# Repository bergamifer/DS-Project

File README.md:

# DS-Project — Beamforming Audio (firmware + hardware)

Sistema de audio beamforming de 32 canales basado en **STM32H743** + **ESP32-C3-MINI-1**.
Control via WiFi (HTTP), pipeline DMA circular, latencia ~20 ms extremo a extremo.

Es el hardware de **Domosónica**, una instalación sonora de ~500 parlantes: cada placa es
un nodo autónomo de 32 canales, y la obra son ~18 nodos en red.

> **Repo unificado (2026-07-03):** este repo (antes `DS-Firmware`, ahora **privado**
> como `DS-Project`) incorpora el proyecto KiCad de hardware completo en
> [`hardware/DS/`](hardware/DS/) — historial de commits preservado vía `git subtree`
> desde el repo `DS` original. Un solo lugar para firmware (STM32 + ESP32) y diseño
> de PCB.

> **¿Primera vez con el equipo?** Empezá por la [guía de uso y conexionado](docs/guia_operacion.md) —
> está escrita en lenguaje llano, sin dar por sabido nada de audio ni de electrónica.
> Y antes de encender amplificadores con micrófonos enchufados, leé
> [qué modos hacen acople](tools/README.md).

---

## Dónde está el proyecto hoy (2026-09-11)

| | Estado |
|---|---|
| **DS11** | **En operación, 3 placas.** 32 canales poblados, audio limpio, soak de 19,6 h |
| **DS12** | **En diseño.** Es la tirada de 10 unidades. Etapa de fuente rediseñada, auditoría cerrada |
| Beamforming | Implementado y **medido**: contraste +17,7 dB dentro/fuera del foco |
| Banco de medición | Dos micrófonos fijos sobre trama TDM común — el foco se verifica con números, no a oído |
| App iOS / sitio público | Andando ([`ios/`](ios/), [`sitio/`](sitio/)) |

El registro de por qué se decidió cada cosa está en los reportes mensuales:
[julio](docs/reporte_2026-07.md) · [agosto](docs/reporte_2026-08.md) · [septiembre](docs/reporte_2026-09.md).

---

## Hardware

| Componente | Detalle |
|---|---|
| MCU | STM32H743VIT6 (LQFP100), Cortex-M7 @ 480 MHz, VOS0 |
| WiFi Bridge | ESP32-C3-MINI-1 (UART4 @ 115200, PA0/PA1) |
| DACs | 4× PCM1690 (8ch TDM8 c/u) = 32 canales — I2C1: 0x98, 0x9C, 0x9A, 0x9E |
| ADC | AK5538VN (8ch TDM256) via SAI3_B — I2C3 addr 0x22 (7-bit 0x11) |
| Amps | 32× PAM8302A Class-D 2.5W (shutdown compartido PD3) |
| EEPROM | CAT24C256 (I2C4 PB6/PB7 **AF6**, WP=PB5) |
| Power | 20V → buck → 5VA → 3.3V/3.3VA (DS12: dos bucks en paralelo; fuente de 24 V, nunca más de 25,5 V: `hardware/DS/DS12_ENTRADA_24V.md`) |

> En DS12 la etapa de fuente cambia entera: el buck pasa a **AP63356** y el LDO digital
> desaparece. El diseño completo, con valores y por qué, está en
> [`hardware/DS/DS12_ALIMENTACION.md`](hardware/DS/DS12_ALIMENTACION.md).

---

## Arquitectura de Audio

```
AK5538VN (ADC 8ch)
    |  TDM256 32-bit @ 48 kHz (config TDM por I2C3, addr 0x22)
    v
SAI3_B RX (Master) --- DMA1_Stream4 --> audio_buffer_3b_rx (RAM_D2)
    |
    v
delay_line[8][1024]   <- circular, 8 canales
    |  Process_ADC_Half() deinterleave + (>>8 a 24-bit)
    v
Fill_Audio_Beamform()   <- per-channel: delay / gain[0-255] / mute
    |                       (test tone -30dBFS cuando test_tone_enabled=1)
    |---> SAI1_A + SAI1_B  (ch 0-15)   DMA1_Stream0 / Stream3
    '---> SAI2_A + SAI2_B  (ch 16-31)  DMA1_Stream1 / Stream2
              |
              v
        4× PCM1690 DAC --> 32× PAM8302A --> parlantes
```

**Latencia total:** ~20,1 ms (10 ms DMA input + ~0,13 ms compute + 10 ms DMA output)

> **⚠️ Alineamiento SAI:** con `DataSize=24` el SAI transmite bits [23:0] (right-aligned).
> Los samples se escriben directo, **sin `<<8`**. El `<<8` erróneo (heredado de DS9) causaba
> la distorsión "tipo 50 kHz" — ver bring-up findings §1.

---

## SAI — pinout DS10/DS11 (idéntico; DS10 corrigió los errores de DS9)

| Bloque | Modo | Pines (AF) | Canales | DMA |
|---|---|---|---|---|
| SAI1_A | Master TX TDM8 | PE4(FS) PE5(SCK) PE6(SD) — AF6 | 0-7 | DMA1_S0 req87 |
| SAI1_B | Slave TX sync | PE3(SD) — AF6 | 8-15 | DMA1_S3 req88 |
| SAI2_A | Master TX TDM8 | PD12(FS) PD13(SCK) PD11(SD) — AF10 | 16-23 | DMA1_S1 req89 |
| SAI2_B | Slave TX sync | PE11(SD) — AF10 | 24-31 | DMA1_S2 req90 |
| SAI3_B | Master RX TDM256 | PD8(SCK) PD9(SD) PD10(FS) — AF6 | ADC 8ch | DMA1_S4 req114 |
| PE2 | MCLK out (24.576 MHz) | SAI1_MCLK_A — AF6 | — | — |

Mapa completo de pines: [docs/pin_map.md](docs/pin_map.md).

---

## ESP32-C3 — Protocolo UART

Trama binaria @ 115200 8N1 (GPIO0 TX → PA1 RX, GPIO1 RX ← PA0 TX):

```
[0xAA][0x55][CMD][LEN_L][LEN_H][PAYLOAD...][XOR_CHECKSUM][0x0D][0x0A]

CMD 0x01 = UPDATE_CFG (52 bytes payload)
  Byte  0    : master_gain (0-255)
  Byte  1    : mute_global (0/1)
  Bytes 2-33 : delays[16] x uint16 LE
  Bytes 34-49: gains[16]  x uint8      (0-255, 0xFF = unity)
  Bytes 50-51: mutes      x uint16 LE  (bitfield ch0-15)
```

HTTP endpoints: `POST /command` (config JSON), `GET /status`, `GET /ping`

> **Trampa de la API:** `POST /reset` **no reinicia el chip** — es un reset de fábrica, y
> deja la placa en modo 0, que es el del acople. Para reiniciar de verdad: `make ota`.

---

## Build & Flash

```bash
# STM32 (firmware principal) — TARGET = ds11_beamforming
cd firmware && make -j4
make flash-stlink            # st-flash --reset (arranca solo)
make todo-cube               # bootloader + app con CubeProgrammer
make ota OTA_HOST=192.168.100.77   # por WiFi, sin cables

# Debug serial: UART7 (PE7/PE8) → J7 → VCP del ST-Link
screen /dev/cu.usbmodemXXXX 115200

# ESP32-C3
. $HOME/esp/esp-idf/export.sh
cd firmware_esp32c3 && idf.py flash monitor -p /dev/cu.usbmodemYYYY
# o, desde firmware/:  make esp-flash
```

⚠️ **`st-flash` no sirve en todas las placas** — en la segunda y la tercera hay que usar
CubeProgrammer (`make todo-cube`). Ver las notas de cada placa en la memoria del proyecto.

**La app vive en `0x08020000`, no en `0x08000000`**: hay un bootloader propio adelante
(ver [docs/ota_wifi.md](docs/ota_wifi.md)).

---

## Estructura del Repositorio

```
hardware/DS/                    # Proyecto KiCad completo (historial propio via subtree)
  DS.kicad_pro/.kicad_sch/.kicad_pcb   # Esquematico + PCB activo
  DS.kicad_dru                  # Reglas de diseño propias (el QFN de IC3) — ver el README de ahi
  DS12_CHECKLIST.md             # LA LISTA PARA TILDAR mientras se dibuja — el indice de los otros tres
  DS12_ALIMENTACION.md          # LA ETAPA DE FUENTE de la DS12: que comprar y como dibujarla
  DS12_PLANNING.md              # Backlog de la DS12 (geometria 2x16, arnes, correcciones)
  DS12_AUDITORIA.md             # Auditoria previa a fabricar: 12 dimensiones, solo lo verificado
  DS12_USB_STM32.md             # USB del STM32 (PA11/PA12 hoy al aire)
  DS11_RELEASE.md               # El KiCad de lo que se fabrico, verificado contra los gerbers
  DS11_PLANNING.md, DS10_*.md   # Historico de revisiones
  jlcpcb/production_files/      # BOM y CPL REALES — la verdad sobre part numbers, no el netlist
  DS.txt                        # Netlist exportado (entrada de tools/netlist_digest.py)
  datasheets/, librerias/, 3d/, plot/, Versiones/

firmware/                       # STM32H743 — make -j4, TARGET=ds11_beamforming
  Core/Src/main.c               # Pipeline SAI/DMA + beamforming + AUTOFOCUS + geometria del array
  Core/Src/uart_protocol.c      # Protocolo binario ESP32<->STM32
  Core/Src/pcm1690.c            # Driver I2C de los 4 DAC
  Core/Src/eeprom_config.c      # Persistencia de config (I2C4 AF6)
  Core/Inc/pin_definitions.h    # Fuente de verdad de todos los pines

firmware_esp32c3/               # ESP32-C3: WiFi + HTTP + puente UART + UI web embebida

tools/                          # Herramientas de host (medicion + hardware) — ver tools/README.md
  check_pcb.sh                  # HOOK: impide commitear gerbers con el cobre desactualizado
  netlist_digest.py             # Convierte DS.txt en tres archivos grepables
  geometria_array.py            # Las 32 posiciones de parlante + DXF del panel, leidas de main.c
  nivel.py abx.py fase.py ...   # Medicion acustica por HTTP (ninguna enciende amps sola)

docs/
  guia_operacion.md             # GUIA DE USO en lenguaje llano
  manual_modos.md               # Los modos de operacion, uno por uno
  reporte_2026-0{7,8,9}.md      # El camino recorrido y por que se decidio cada cosa
  banco_dos_microfonos.md       # El banco de medicion de dos microfonos
  protocolo_medicion.md         # Metodologia acustica (mic fijo, foco movil)
  ds11_errata.md                # Los cortos de fabrica de la DS11 — leer antes de mandar a producir
  ds11_perf.md                  # Performance del pipeline (caches, -O2, soak)
  pin_map.md, memory_map.md     # Pines y layout de RAM (regla DMA vs DTCM)
  ak5538vn_ref.md, pcm1690_ref.md, gpio_control.md, audio_architecture.md
  ota_wifi.md, multinode.md, app_ios.md, instalacion_15_nodos.md
  stm32/                        # Referencia RM0433 (clocks, SAI, DMA, I2C, GPIO)
  datos/                        # Mediciones crudas en JSON + el .md que dice que se medía
  img_osc/, media/              # Capturas de osciloscopio y video
  historico/                    # Bring-up DS10 + esquematico DS9
  pdf/                          # Plantilla y script para generar la guia en PDF

datasheets/                     # Hojas de datos del MCU y los chips de audio
webserver/                      # Control web multi-dispositivo (Flask + SQLite)
sitio/                          # Pagina publica del proyecto
ios/                            # App "Domosonica" (SwiftUI)
mecenazgo/                      # ~320 MB de comprobantes — FUERA de git a proposito
```

**Fuera del repo a propósito:** `firmware/build*/`, `firmware_esp32c3/build/`,
`webserver/venv/`, `mecenazgo/`, `.ds12_audit/` (derivado del netlist), `*.wav`,
`docs/pdf/*.pdf` (se regenera con `docs/pdf/hacer_pdf.sh`), y `secrets.h`.

---

## Antes de mandar una placa a producir

```bash
tools/check_pcb.sh --install    # una sola vez por copia del repo
```

Instala un hook de pre-commit que corre el DRC dos veces —con los rellenos guardados y
con `--refill-zones`— y **bloquea el commit si el cobre guardado está viejo**. KiCad no
recalcula los rellenos al plotear: usa lo que está guardado. Ese mecanismo ya arruinó dos
tandas de la DS11 ([docs/ds11_errata.md](docs/ds11_errata.md)) y apareció una tercera vez,
latente, en septiembre.

Al exportar los gerbers, además: `kicad-cli pcb export gerbers --check-zones` (viene
apagado por default).

---

## Issues Conocidos

| Problema | Estado |
|---|---|
| Skew de fase entre SAI1 y SAI2 (ch0-15 vs 16-31) | Medido: **4 µs** entre bancos. Sync por SAI_GCR si algún día molesta |
| Protocolo ESP32: config de 16ch / mutes 16-bit | `CMD_SET_BEAM`/`CMD_SET_MODE` cubren el uso normal; raw de 32ch pendiente |
| Underruns residuales (~4) en el bloque verboso de cada 10 s | Benignos (el DMA reusa el half-buffer) |
| PA11/PA12 (USB_DM/DP del STM32) al aire | Ver [DS12_USB_STM32.md](hardware/DS/DS12_USB_STM32.md) |
| Prueba de escucha del `-O2` | Pendiente desde la mejora de 43× del pipeline |

---

## Próximos Pasos

1. **Cerrar la DS12 y mandar a producir las 10 placas** — etapa de fuente + los ítems de
   esquemático del §3 de [DS12_AUDITORIA.md](hardware/DS/DS12_AUDITORIA.md)
2. Cortar y armar los nodos con la geometría **2×16** (el firmware ya la soporta:
   `SPK_LAYOUT_2X16` en `main.c`)
3. Control de volumen/balance per-canal vía ESP32 (registros 72-79 del PCM1690, hoy fijos
   en −24 dB por `PCM1690_ATTEN_DEFAULT`)
4. Instalación multi-nodo: [docs/multinode.md](docs/multinode.md) y
   [docs/instalacion_15_nodos.md](docs/instalacion_15_nodos.md)

---

**Última actualización:** 2026-09-11 — auditoría DS12 aplicada, orden del repo, hook de PCB.

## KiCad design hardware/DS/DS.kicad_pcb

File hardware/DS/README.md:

# Domosónica — la placa DS

Sistema de audio espacial de 32 canales con capacidad de beamforming, diseñado para instalaciones artísticas a gran escala.

---

## El proyecto

**Domosonica** es una instalación sonora inmersiva basada en un campo de ~500 parlantes distribuidos en el espacio. El objetivo es crear experiencias de escucha donde el sonido se percibe como un fenómeno espacial: fuentes que se mueven, campos que emergen, focos que aparecen y desaparecen en el espacio físico.

El beamforming permite dirigir energía sonora hacia puntos específicos del espacio sumando señales con retardos calculados. Con suficientes parlantes y resolución de fase, es posible construir frentes de onda arbitrarios — lo que convierte el espacio en un instrumento.

### Por qué hardware propio

La escala del proyecto (~500 parlantes) hace inviable el uso de hardware de audio profesional estándar: demasiado costoso, demasiado grande, demasiado dependiente de infraestructura. La placa DS es una solución diseñada específicamente para esta instalación: barato, compacto, reproducible, y capaz de operar en red distribuida.

---

## La placa, por unidad

Cada unidad es un nodo de audio autónomo que distribuye 32 canales amplificados hacia 32 parlantes. La instalación completa usa ~18 unidades conectadas en red.

```
                         DS (por unidad)
┌────────────────────────────────────────────────────────┐
│                                                        │
│  20V DC ──> Buck ──> 5V ──> 32x PAM8302A ──> Speakers │
│              │                                         │
│              └──> LDOs ──> STM32H743 ──SAI──> 4x DAC  │
│                                │                       │
│                            ESP32-C3  (WiFi/BLE)        │
│                                │                       │
│                            AK5538VN  (8ch ADC)         │
│                                                        │
└────────────────────────────────────────────────────────┘
         ↑                              ↑
    20V daisy-chain              Cat5e/RJ45 audio
    entre cajas                  (4 links × 8ch = 32ch)
```

### Capacidades por unidad

- **32 canales de salida** — DAC diferencial 32-bit + amp Class-D 2.5W por canal
- **8 canales de entrada** — ADC diferencial 32-bit (micrófonos o señal de referencia)
- **Sincronización de red** — MCLK 24.576MHz (512xfS) compartido garantiza coherencia de fase entre unidades
- **WiFi/BLE** — configuración y control inalámbrico
- **Alimentación 20V** — bus daisy-chain entre cajas, un solo cable de potencia

### Escala del sistema completo

| | Por unidad | Sistema (18 unidades) |
| --- | --- | --- |
| Canales de salida | 32 | ~576 |
| Canales de entrada | 8 | ~144 |
| Parlantes | 32 | ~500 |
| Alimentación | 20V DC | Bus daisy-chain |

---

## Beamforming

El beamforming en este contexto no es telecomunicaciones — es síntesis de campo sonoro. La idea central es que si conocés la posición de cada parlante y podés controlar la fase y amplitud de cada canal de forma independiente, podés construir patrones de interferencia específicos en el espacio.

**Aplicaciones concretas en la instalación:**

- Focos de sonido: energía concentrada en un punto del espacio
- Fuentes virtuales: la percepción de que el sonido viene de un lugar donde no hay parlante
- Zonas silenciosas: cancelación activa por interferencia destructiva
- Movimiento: barrido de un frente de onda a través del espacio

El STM32H743 corre a 480MHz con DMA audio pipeline y opera los 5 puertos SAI simultáneamente sin underruns, lo que permite actualizar los 32 canales en tiempo real a 48kHz.

---

## Hardware

### Componentes principales

| IC | Función | Bus |
| --- | --- | --- |
| STM32H743VIT6 | MCU central, 480MHz, LQFP100 | — |
| 4× PCM1690 | DAC 8ch diferencial 32-bit | SAI1/SAI2 |
| AK5538VN | ADC 8ch diferencial 32-bit | SAI3_B (TDM256) |
| 32× PAM8302A | Amplificador Class-D 2.5W/ch | — |
| ESP32-C3-Mini | WiFi / BLE | UART |
| MP2315S | Buck 20V→5V 3A | — |

> **En DS12 la etapa de fuente cambia entera:** el buck pasa a **AP63356** y el LDO digital
> desaparece. Todo el diseño, con valores y con el porqué de cada uno, en
> [DS12_ALIMENTACION.md](DS12_ALIMENTACION.md).
>
> **Entrada de la DS12: 24 V, ajustada a 24,0 V y nunca más de 25,5 V** (decidido el 2026-10-23;
> detalle en [DS12_ENTRADA_24V.md](DS12_ENTRADA_24V.md)). Por debajo de ~15 V los amplificadores
> no encienden (el micro sí); por encima de ~26,7 V conduce el TVS y puede abrirse el fusible.
> **Esa regla es sólo de la DS12.** La DS11 nunca va a 24 V: su buck MP2315S aguanta 26 V como
> máximo absoluto. Antes este párrafo decía «20 V, ventana 15–21 V, 24 V no sirve»: ya no vale.

### PCB

- 4 capas, FR-4, 1.6mm — stackup JLC04161H-7628
- Fabricado por JLCPCB
- Diseñado en **KiCad 10.0** (el archivo dice `generator_version "10.0"`)

### Distribución de audio

Señal diferencial sobre Cat5e/RJ45 en topología daisy-chain. 4 pares trenzados por cable = 4 canales diferenciales. 2 cables por placa = 8 canales por enlace × 4 enlaces = 32 canales.

---

## Estado (2026-09-11)

| Versión | Estado |
| --- | --- |
| DS9 | Histórico — sistema base, PCM1802 2ch ADC |
| DS10 | Histórico. Tanda de 3, **defectuosa**: JLCPCB montó 3 de 4 DACs rotados 180°. Reclamo cerrado (USD 355). Ver [DS10_BRINGUP.md](DS10_BRINGUP.md) §6 |
| **DS11** | **En operación — 3 placas**, 32 canales poblados y audio limpio. El KiCad de lo que se fabricó está verificado contra los gerbers en [DS11_RELEASE.md](DS11_RELEASE.md) (tag `ds11-release`) |
| **DS12** | **En diseño — es la tirada de 10 unidades.** Fuente rediseñada, geometría 2×16, auditoría cerrada |

### Mejoras DS10 respecto a DS9

- PCM1802 (2ch) reemplazado por AK5538VN (8ch, 32-bit) — 4× más entradas
- 32× PAM8302A integrados en PCB (antes módulo HAT externo)
- Fuente 20V con buck local por placa (antes fuente externa)
- Supply analógico separado (+3.3VA) para el ADC

---

## Documentación técnica

### DS12 — lo que se está diseñando ahora

- **[DS12_DECISIONES.md](DS12_DECISIONES.md) — qué está decidido, qué se descartó y qué sigue
  abierto**, en una página. Empezar por acá; los demás son el porqué de cada fila
- **[DS12_CHECKLIST.md](DS12_CHECKLIST.md) — la lista para tildar mientras dibujás.**
  El índice de todo lo de abajo, en orden de dibujo: qué poner y dónde está el porqué
- [DS12_ALIMENTACION.md](DS12_ALIMENTACION.md) — **La etapa de fuente, lista para dibujar.**
  Qué integrado va en cada lugar, con qué divisor, y por qué. Incluye §6.1: los dos modos
  de falla que *crea* el rediseño y el BAT54 de US$ 0,03 que los cierra
- [DS12_PLANNING.md](DS12_PLANNING.md) — Backlog: geometría 2×16, arnés, polaridad de los
  conectores de parlante (`+ − − +`), correcciones al esquemático
- [DS12_AUDITORIA.md](DS12_AUDITORIA.md) — Auditoría previa a fabricar. Doce dimensiones,
  y **sólo lo que sobrevivió a verificación**: cada ítem dice cómo se comprobó
- [DS12_USB_STM32.md](DS12_USB_STM32.md) — El USB del STM32 (PA11/PA12 hoy al aire)
- [DS12_MICROFONO_DNP.md](DS12_MICROFONO_DNP.md) — Micrófonos MEMS I2S DNP (MSM261S4030H0R): uno en el STM32 (I2S2) y uno en el ESP32 (GPIO6/7/3)
- [DS12_CAMARA_DVP_FUTURO.md](DS12_CAMARA_DVP_FUTURO.md) — Cámara DVP/MIPI: **no entra en la DS12** (D4–D7 caen sobre el audio); idea archivada, con el cruce de pines
- [DS12_REVISION_DECISIONES.md](DS12_REVISION_DECISIONES.md) — **Revisión del 2026-11-10** de las decisiones recientes
  (24 V, LEDs de J9, R20, bias del ADC, micrófono): qué se sostiene, dos errores a corregir y una mejora
- [DS12_REVISION_ALIMENTACION.md](DS12_REVISION_ALIMENTACION.md) — **Revisión de la
  alimentación (octubre 2026)**: las fuentes y cómo conviven, contra las hojas de datos, con
  refutación a ciegas. Los planes que la guían son
  [DS12_REVISION_ALIMENTACION_PLAN.md](DS12_REVISION_ALIMENTACION_PLAN.md) y
  [DS12_REVISION_ALIMENTACION_RONDA2.md](DS12_REVISION_ALIMENTACION_RONDA2.md). Las cuentas y
  simulaciones están en [revision_alimentacion/](revision_alimentacion/), todas con autoprueba

### Histórico

- [DS11_RELEASE.md](DS11_RELEASE.md) — Qué se fabricó exactamente, verificado byte a byte
- [DS11_PLANNING.md](DS11_PLANNING.md) — Plan de la revisión DS11
- [DS10_DESIGN_REVIEW.md](DS10_DESIGN_REVIEW.md) — Revisión de diseño y verificación de netlist
- [DS10_BRINGUP.md](DS10_BRINGUP.md) — Bring-up + defectos confirmados de la tanda 1
- [DS10_PRE_PRODUCTION_CHECKLIST.md](DS10_PRE_PRODUCTION_CHECKLIST.md) — Checklist y parámetros JLCPCB
- `Versiones/` — Snapshots del proyecto KiCad tal como se fabricó cada revisión

---

## Cómo está armada la carpeta

| | |
|---|---|
| `DS.kicad_pro/.kicad_sch/.kicad_pcb` | El proyecto activo |
| `DS.kicad_dru` | **Reglas de diseño propias.** Hoy: los 0,1414 mm entre pads del QFN-64 de IC3, que son geometría del footprint y no un ruteo apretado. KiCad lo lee solo por llamarse igual que el proyecto |
| `jlcpcb/production_files/` | **BOM y CPL reales.** La verdad sobre part numbers comprados vive acá, **no** en el netlist: para el 4,7 nF, `DS.txt` dice `C883564` y el BOM dice `C2961271` |
| `DS.txt` | Netlist exportado. Entrada de `tools/netlist_digest.py`, que lo convierte en tres archivos grepables |
| `datasheets/` | Hojas de datos de los componentes de la placa. Las del MCU y los chips de audio están en `../../datasheets/` |
| `librerias/`, `3d/`, `plot/`, `CNC/` | Símbolos y footprints propios, modelos 3D, PDFs del esquemático, corte de la caja |

### Antes de exportar gerbers

```bash
tools/check_pcb.sh --install    # una vez por copia del repo
```

KiCad **no recalcula los rellenos de zona al plotear**: usa el cobre guardado en el
`.kicad_pcb`. Ese mecanismo ya arruinó dos tandas de la DS11
([docs/ds11_errata.md](../../docs/ds11_errata.md)) y apareció una tercera vez en septiembre.
El hook lo verifica solo. Y al exportar: `kicad-cli pcb export gerbers --check-zones`.

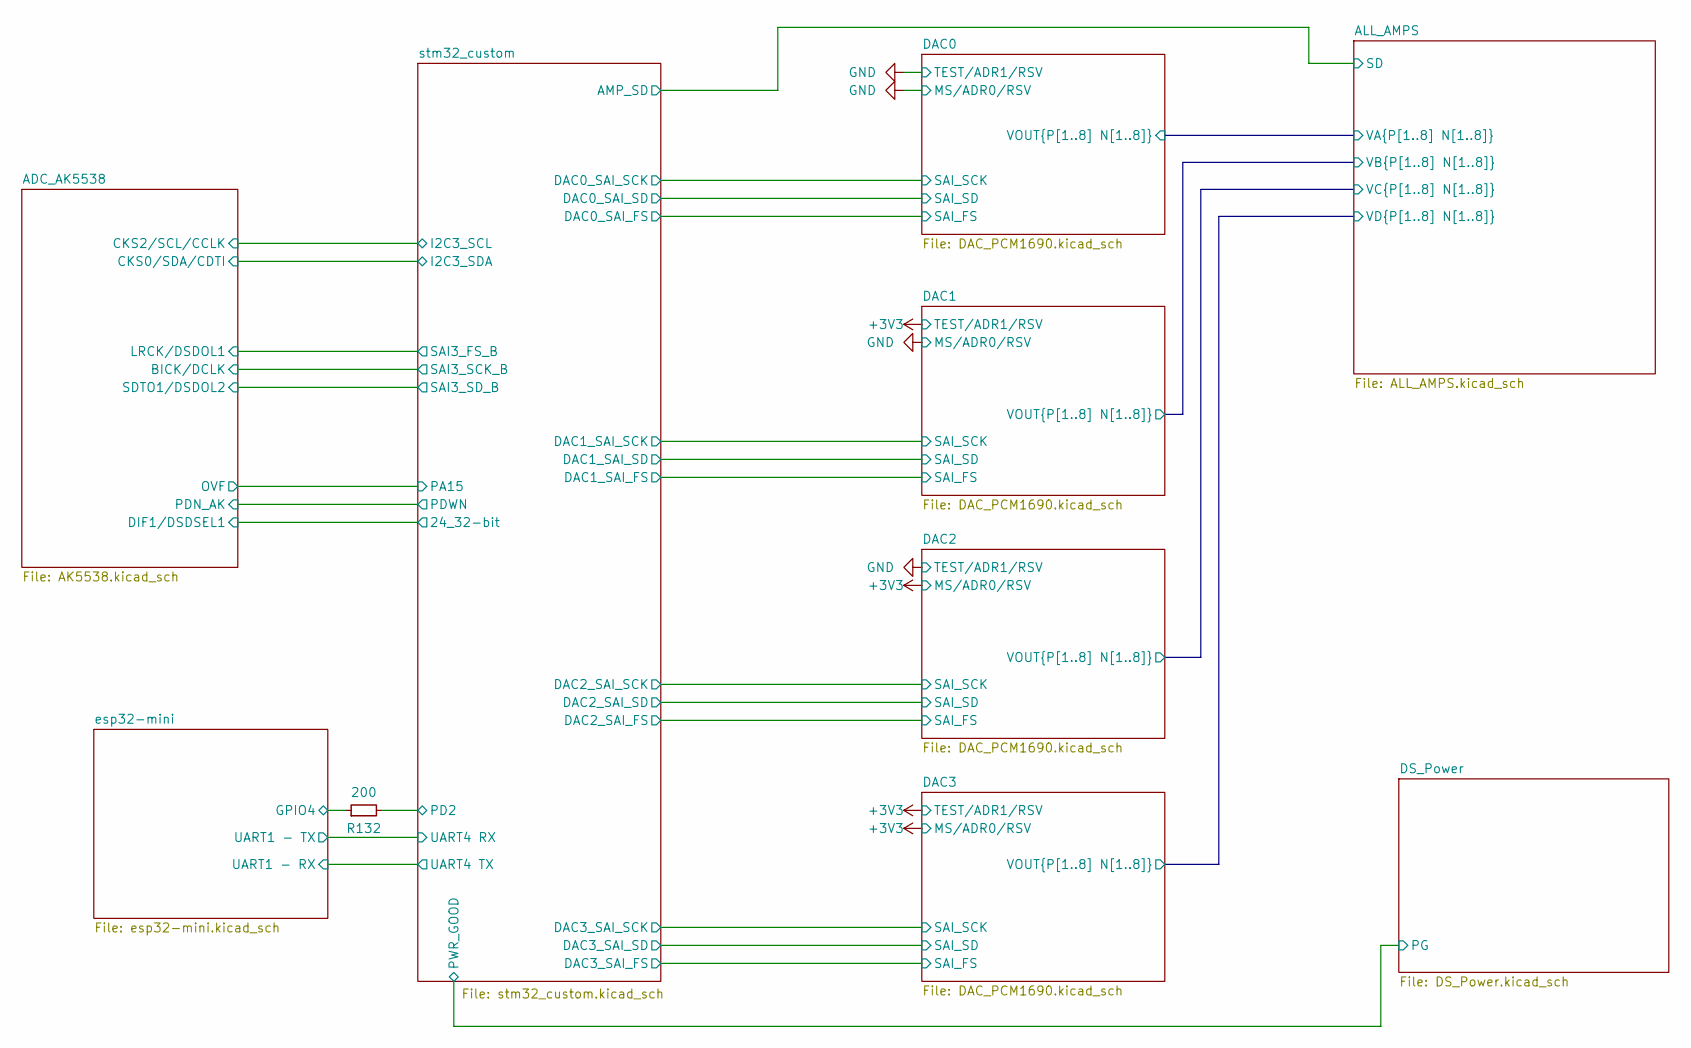
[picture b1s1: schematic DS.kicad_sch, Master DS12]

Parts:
R132: 200; R_0603_1608Metric; Mouser part 594-MCT06030C1200FP5

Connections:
/esp32-mini/GPIO4: R132.1; also elsewhere on the board
/stm32_custom/PD2: R132.2; also elsewhere on the board

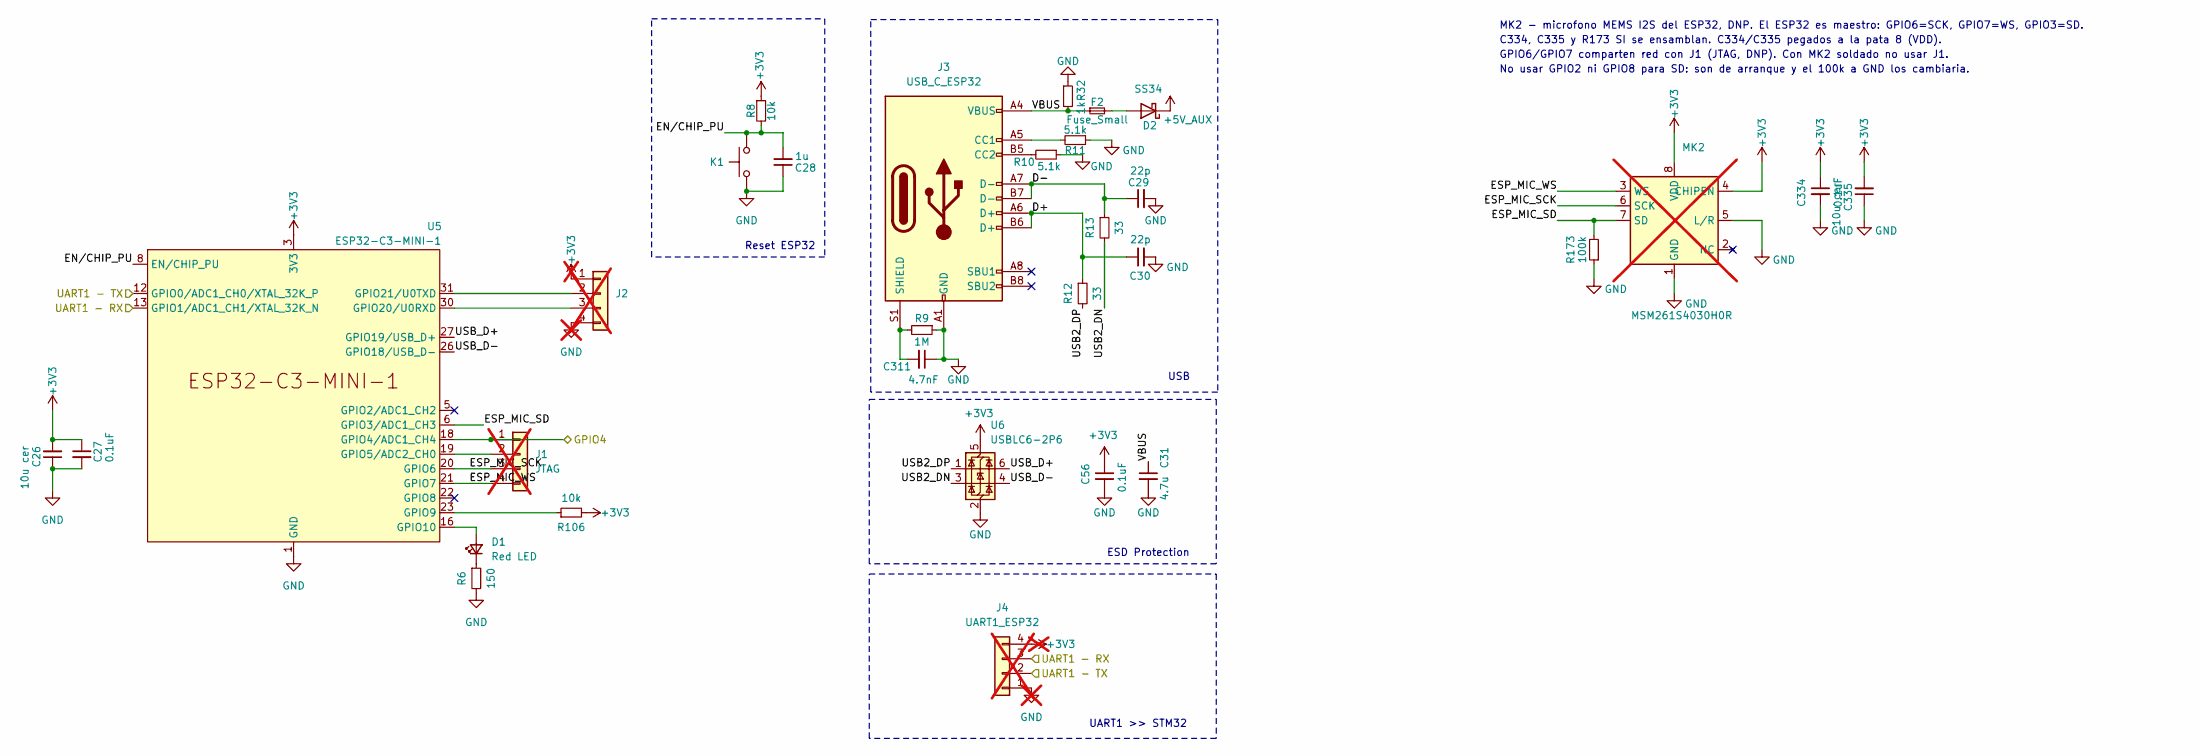
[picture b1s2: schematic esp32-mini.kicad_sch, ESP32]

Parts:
C26, C335: 10u cer; C_0603_1608Metric; Mouser part 187-CL10A106MA8NRWC
C27, C56, C334: 0.1uF; C_0402_1005Metric; Mouser part 581-KGM15BR71E104KT
C28: 1u; C_0603_1608Metric; Mouser part 791-0603B105M160CT
C29, C30: 22p; C_0402_1005Metric; Mouser part 581-KGM15ACG1E220JT
C31: 4.7u; C_0603_1608Metric; Mouser part 581-06036C475KAT2A
C311: 4.7nF; C_0603_1608Metric; Manufacturer_Part_Number GCM1885C1H472GA16D; LCSC C2961271
D1: Red LED; LED_0805_2012Metric; Mouser part 720-BPS2THVG2J8L55S
D2: SS34; D_SMA; Manufacturer_Part_Number SS14HE; LCSC C8678
F2: Fuse_Small; Fuse_1206_3216Metric; Manufacturer_Part_Number SMD1206P110TF/16; LCSC C523825
J1: JTAG; JST_XH_B4B-XH-A_1x04_P2.50mm_Vertical; Manufacturer_Part_Number B4B-XH-A; not fitted
J2: UART0_ESP32; JST_XH_B4B-XH-A_1x04_P2.50mm_Vertical; Manufacturer_Part_Number B4B-XH-A; LCSC C594232; not fitted
J3: USB_C_ESP32; USB_C_Receptacle_G-Switch_GT-USB-7051x; Mouser part 538-217179-0001
J4: UART1_ESP32; JST_XH_B4B-XH-A_1x04_P2.50mm_Vertical; Manufacturer_Part_Number B4B-XH-A; not fitted
K1: BOOT ESP32; SW_SPST_EVQP2_MiddlePushTravel_H2.5mm; Manufacturer_Part_Number TS-1185-W-4P-H1.8-160; LCSC C51927445
MK2: MSM261S4030H0R; Manufacturer_Part_Number MSM261S4030H0R; not fitted
R6: 150; R_0603_1608Metric; Manufacturer_Part_Number 0603WAF1500T5E; LCSC C22808
R8, R106: 10k; R_0402_1005Metric; Mouser part 603-RC0603JR-1310KL
R9: 1M; R_0603_1608Metric; Mouser part 603-RC0603FR-131ML
R10, R11: 5.1k; R_0603_1608Metric; Mouser part 708-RMCF0603FT5K10
R12, R13: 33; R_0603_1608Metric; Mouser part 71-CRCW060333R0FKEAC
R32: 1k; R_0402_1005Metric; Manufacturer_Part_Number CRCW06031K00FKEA; LCSC C11702
R173: 100k; R_0402_1005Metric; LCSC C25741
U5: ESP32-C3-MINI-1; Manufacturer_Part_Number ESP32-C3-MINI-1-N4; LCSC C2838502
U6: USBLC6-2P6; SOT-666; Manufacturer_Part_Number USBLC6-2P6; LCSC C15999

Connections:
+3V3: C26.2, C27.1, C56.1, C334.1, C335.2, J2.1, J4.4, MK2.4 (CHIPEN), MK2.8 (VDD), R8.1, R106.2, U5.3 (3V3), U6.5 (VBUS); also elsewhere on the board
+5V_AUX: D2.1 (K); also elsewhere on the board
/esp32-mini/D+: C30.1, J3.A6 (D+), J3.B6 (D+), R12.1
/esp32-mini/D-: C29.1, J3.A7 (D-), J3.B7 (D-), R13.1
/esp32-mini/EN/CHIP_PU: C28.2, K1.2, R8.2, U5.8 (EN/CHIP_PU)
/esp32-mini/GPIO4: J1.1, U5.18 (GPIO4/ADC1_CH4); also elsewhere on the board
/esp32-mini/UART1 - RX: J4.3, U5.13 (GPIO1/ADC1_CH1/XTAL_32K_N); also elsewhere on the board
/esp32-mini/UART1 - TX: J4.2, U5.12 (GPIO0/ADC1_CH0/XTAL_32K_P); also elsewhere on the board
/esp32-mini/USB2_DN: R13.2, U6.3 (I/O2)
/esp32-mini/USB2_DP: R12.2, U6.1 (I/O1)
/esp32-mini/USB_D+: U5.27 (GPIO19/USB_D+), U6.6 (I/O1)
/esp32-mini/USB_D-: U5.26 (GPIO18/USB_D-), U6.4 (I/O2)
/esp32-mini/VBUS: C31.1, F2.1, J3.A4 (VBUS), J3.A9 (VBUS), J3.B4 (VBUS), J3.B9 (VBUS), R32.2
GND: C26.1, C27.2, C28.1, C29.2, C30.2, C31.2, C56.2, C311.1, C334.2, C335.1, J2.4, J3.A1 (GND), J3.A12 (GND), J3.B1 (GND), J3.B12 (GND), J4.1, K1.1, MK2.1 (GND), MK2.5 (L/R), R6.2, R9.1, R10.1, R11.1, R32.1, R173.1, U5.1 (GND), U5.2 (GND), U5.11 (GND), U5.14 (GND), U5.36 (GND), U5.37 (GND), U5.38 (GND), U5.39 (GND), U5.40 (GND), U5.41 (GND), U5.42 (GND), U5.43 (GND), U5.44 (GND), U5.45 (GND), U5.46 (GND), U5.47 (GND), U5.48 (GND), U5.49 (GND), U5.50 (GND), U5.51 (GND), U5.52 (GND), U5.53 (GND), U6.2 (GND); also elsewhere on the board
unnamed: D1.2 (A), U5.16 (GPIO10)
unnamed: D1.1 (K), R6.1
unnamed: D2.2 (A), F2.2
unnamed: J3.A5 (CC1), R11.2
unnamed: J3.B5 (CC2), R10.2
unnamed: C311.2, J3.S1 (SHIELD), R9.2
unnamed: MK2.7 (SD), R173.2, U5.6 (GPIO3/ADC1_CH3)
unnamed: J1.2, U5.19 (GPIO5/ADC2_CH0)
unnamed: J1.3, MK2.6 (SCK), U5.20 (GPIO6)
unnamed: J1.4, MK2.3 (WS), U5.21 (GPIO7)
unnamed: R106.1, U5.23 (GPIO9)
unnamed: J2.3, U5.30 (GPIO20/U0RXD)
unnamed: J2.2, U5.31 (GPIO21/U0TXD)

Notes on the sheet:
Reset ESP32
ESD Protection
UART1 >> STM32
USB
MK2 - microfono MEMS I2S del ESP32, DNP. El ESP32 es maestro: GPIO6=SCK, GPIO7=WS, GPIO3=SD.
C334, C335 y R173 SI se ensamblan. C334/C335 pegados a la pata 8 (VDD).
GPIO6/GPIO7 comparten red con J1 (JTAG, DNP). Con MK2 soldado no usar J1.
No usar GPIO2 ni GPIO8 para SD: son de arranque y el 100k a GND los cambiaria.

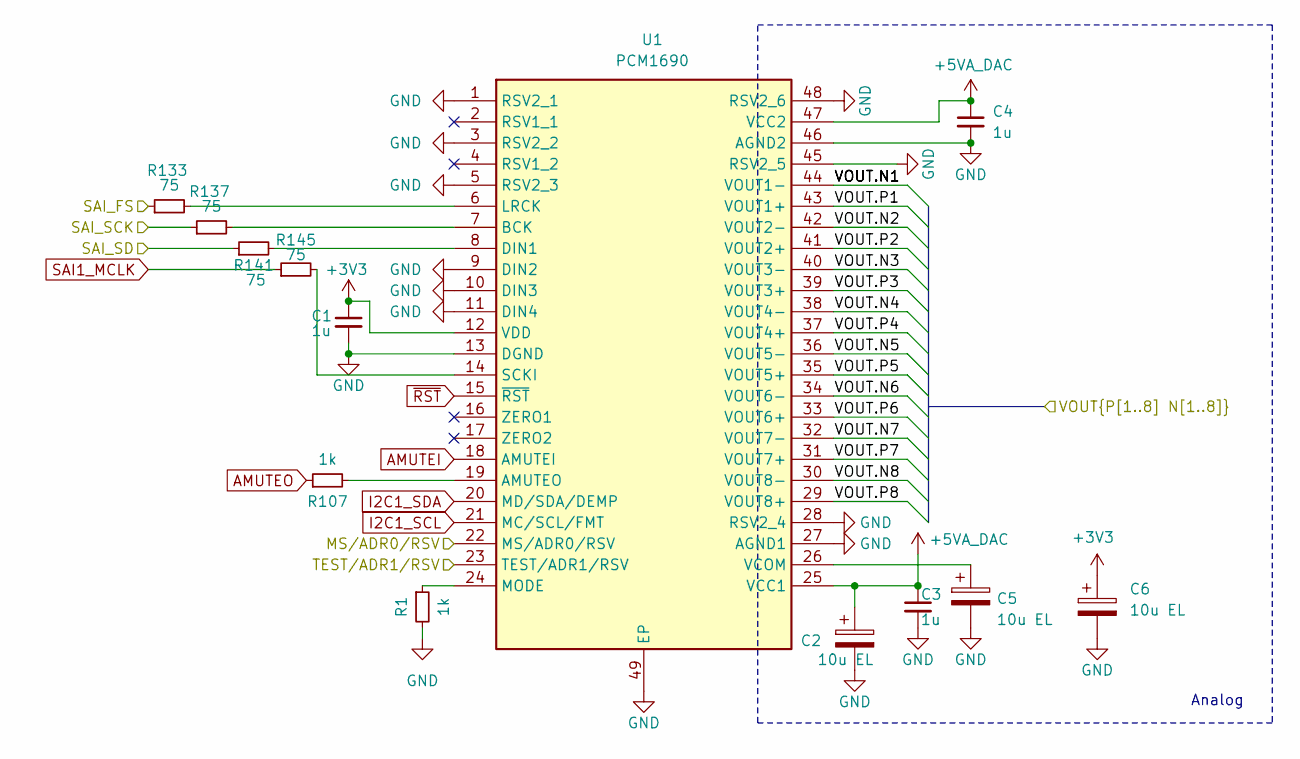
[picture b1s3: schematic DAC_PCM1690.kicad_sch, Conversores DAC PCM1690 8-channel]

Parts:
C1, C3, C4: 1u; C_0603_1608Metric; Mouser part 791-0603B105M160CT
C2, C5, C6: 10u EL; CP_Elec_4x5.7; Manufacturer_Part_Number AEC-SMD-10UF-50V; LCSC C134745
R1, R107: 1k; R_0402_1005Metric; Manufacturer_Part_Number CRCW06031K00FKEA; LCSC C11702
R133, R137, R141, R145: 75; R_0603_1608Metric; Manufacturer_Part_Number 0603WAF750JT5E; LCSC C4275
U1: PCM1690; SOP50P810X120-49N; Mouser part 595-PCM1690DCAR

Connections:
+3V3: C1.1, C6.1, U1.12 (VDD), U1.22 (MS/ADR0/RSV); also elsewhere on the board
+5VA_DAC: C2.1, C3.1, C4.1, U1.25 (VCC1), U1.47 (VCC2); also elsewhere on the board
/ALL_AMPS/VC.N1: U1.44 (VOUT1-); also elsewhere on the board
/ALL_AMPS/VC.N2: U1.42 (VOUT2-); also elsewhere on the board
/ALL_AMPS/VC.N3: U1.40 (VOUT3-); also elsewhere on the board
/ALL_AMPS/VC.N4: U1.38 (VOUT4-); also elsewhere on the board
/ALL_AMPS/VC.N5: U1.36 (VOUT5-); also elsewhere on the board
/ALL_AMPS/VC.N6: U1.34 (VOUT6-); also elsewhere on the board
/ALL_AMPS/VC.N7: U1.32 (VOUT7-); also elsewhere on the board
/ALL_AMPS/VC.N8: U1.30 (VOUT8-); also elsewhere on the board
/ALL_AMPS/VC.P1: U1.43 (VOUT1+); also elsewhere on the board
/ALL_AMPS/VC.P2: U1.41 (VOUT2+); also elsewhere on the board
/ALL_AMPS/VC.P3: U1.39 (VOUT3+); also elsewhere on the board
/ALL_AMPS/VC.P4: U1.37 (VOUT4+); also elsewhere on the board
/ALL_AMPS/VC.P5: U1.35 (VOUT5+); also elsewhere on the board
/ALL_AMPS/VC.P6: U1.33 (VOUT6+); also elsewhere on the board
/ALL_AMPS/VC.P7: U1.31 (VOUT7+); also elsewhere on the board
/ALL_AMPS/VC.P8: U1.29 (VOUT8+); also elsewhere on the board
/DAC2/SAI_FS: R133.1; also elsewhere on the board
/DAC2/SAI_SCK: R137.1; also elsewhere on the board
/DAC2/SAI_SD: R141.1; also elsewhere on the board
AMUTEI: U1.18 (AMUTEI); also elsewhere on the board
AMUTEO: R107.1; also elsewhere on the board
GND: C1.2, C2.2, C3.2, C4.2, C5.2, C6.2, R1.2, U1.1 (RSV2_1), U1.3 (RSV2_2), U1.5 (RSV2_3), U1.9 (DIN2), U1.10 (DIN3), U1.11 (DIN4), U1.13 (DGND), U1.23 (TEST/ADR1/RSV), U1.27 (AGND1), U1.28 (RSV2_4), U1.45 (RSV2_5), U1.46 (AGND2), U1.48 (RSV2_6), U1.49 (EP); also elsewhere on the board
I2C1_SCL: U1.21 (MC/SCL/FMT); also elsewhere on the board
I2C1_SDA: U1.20 (MD/SDA/DEMP); also elsewhere on the board
unnamed: R107.2, U1.19 (AMUTEO)
unnamed: R137.2, U1.7 (BCK)
unnamed: R141.2, U1.8 (DIN1)
unnamed: R133.2, U1.6 (LRCK)
unnamed: R1.1, U1.24 (MODE)
unnamed: R145.2, U1.14 (SCKI)
unnamed: C5.1, U1.26 (VCOM)
SAI1_MCLK: R145.1; also elsewhere on the board
~RST: U1.15 (~RST); also elsewhere on the board

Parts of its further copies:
C7, C9, C10, C13, C15, C16, C19, C21, C22: 1u; C_0603_1608Metric; Mouser part 791-0603B105M160CT
C8, C11, C12, C14, C17, C18, C20, C23, C24: 10u EL; CP_Elec_4x5.7; Manufacturer_Part_Number AEC-SMD-10UF-50V; LCSC C134745
R2, R3, R4, R108, R109, R110: 1k; R_0402_1005Metric; Manufacturer_Part_Number CRCW06031K00FKEA; LCSC C11702
R134, R135, R136, R138, R139, R140, R142, R143, R144, R146, R147, R148: 75; R_0603_1608Metric; Manufacturer_Part_Number 0603WAF750JT5E; LCSC C4275
U2, U3, U4: PCM1690; SOP50P810X120-49N; Mouser part 595-PCM1690DCAR

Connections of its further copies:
+3V3: C7.1, C12.1, C13.1, C18.1, C19.1, C24.1, U2.12 (VDD), U3.12 (VDD), U3.23 (TEST/ADR1/RSV), U4.12 (VDD), U4.22 (MS/ADR0/RSV), U4.23 (TEST/ADR1/RSV); also elsewhere on the board
+5VA_DAC: C8.1, C9.1, C10.1, C14.1, C15.1, C16.1, C20.1, C21.1, C22.1, U2.25 (VCC1), U2.47 (VCC2), U3.25 (VCC1), U3.47 (VCC2), U4.25 (VCC1), U4.47 (VCC2); also elsewhere on the board
/ALL_AMPS/VA.N1: U2.44 (VOUT1-); also elsewhere on the board
/ALL_AMPS/VA.N2: U2.42 (VOUT2-); also elsewhere on the board
/ALL_AMPS/VA.N3: U2.40 (VOUT3-); also elsewhere on the board
/ALL_AMPS/VA.N4: U2.38 (VOUT4-); also elsewhere on the board
/ALL_AMPS/VA.N5: U2.36 (VOUT5-); also elsewhere on the board
/ALL_AMPS/VA.N6: U2.34 (VOUT6-); also elsewhere on the board
/ALL_AMPS/VA.N7: U2.32 (VOUT7-); also elsewhere on the board
/ALL_AMPS/VA.N8: U2.30 (VOUT8-); also elsewhere on the board
/ALL_AMPS/VA.P1: U2.43 (VOUT1+); also elsewhere on the board
/ALL_AMPS/VA.P2: U2.41 (VOUT2+); also elsewhere on the board
/ALL_AMPS/VA.P3: U2.39 (VOUT3+); also elsewhere on the board
/ALL_AMPS/VA.P4: U2.37 (VOUT4+); also elsewhere on the board
/ALL_AMPS/VA.P5: U2.35 (VOUT5+); also elsewhere on the board
/ALL_AMPS/VA.P6: U2.33 (VOUT6+); also elsewhere on the board
/ALL_AMPS/VA.P7: U2.31 (VOUT7+); also elsewhere on the board
/ALL_AMPS/VA.P8: U2.29 (VOUT8+); also elsewhere on the board
/ALL_AMPS/VB.N1: U3.44 (VOUT1-); also elsewhere on the board
/ALL_AMPS/VB.N2: U3.42 (VOUT2-); also elsewhere on the board
/ALL_AMPS/VB.N3: U3.40 (VOUT3-); also elsewhere on the board
/ALL_AMPS/VB.N4: U3.38 (VOUT4-); also elsewhere on the board
/ALL_AMPS/VB.N5: U3.36 (VOUT5-); also elsewhere on the board
/ALL_AMPS/VB.N6: U3.34 (VOUT6-); also elsewhere on the board
/ALL_AMPS/VB.N7: U3.32 (VOUT7-); also elsewhere on the board
/ALL_AMPS/VB.N8: U3.30 (VOUT8-); also elsewhere on the board
/ALL_AMPS/VB.P1: U3.43 (VOUT1+); also elsewhere on the board
/ALL_AMPS/VB.P2: U3.41 (VOUT2+); also elsewhere on the board
/ALL_AMPS/VB.P3: U3.39 (VOUT3+); also elsewhere on the board
/ALL_AMPS/VB.P4: U3.37 (VOUT4+); also elsewhere on the board
/ALL_AMPS/VB.P5: U3.35 (VOUT5+); also elsewhere on the board
/ALL_AMPS/VB.P6: U3.33 (VOUT6+); also elsewhere on the board
/ALL_AMPS/VB.P7: U3.31 (VOUT7+); also elsewhere on the board
/ALL_AMPS/VB.P8: U3.29 (VOUT8+); also elsewhere on the board
/ALL_AMPS/VD.N1: U4.44 (VOUT1-); also elsewhere on the board
/ALL_AMPS/VD.N2: U4.42 (VOUT2-); also elsewhere on the board
/ALL_AMPS/VD.N3: U4.40 (VOUT3-); also elsewhere on the board
/ALL_AMPS/VD.N4: U4.38 (VOUT4-); also elsewhere on the board
/ALL_AMPS/VD.N5: U4.36 (VOUT5-); also elsewhere on the board
/ALL_AMPS/VD.N6: U4.34 (VOUT6-); also elsewhere on the board
/ALL_AMPS/VD.N7: U4.32 (VOUT7-); also elsewhere on the board
/ALL_AMPS/VD.N8: U4.30 (VOUT8-); also elsewhere on the board
/ALL_AMPS/VD.P1: U4.43 (VOUT1+); also elsewhere on the board
/ALL_AMPS/VD.P2: U4.41 (VOUT2+); also elsewhere on the board
/ALL_AMPS/VD.P3: U4.39 (VOUT3+); also elsewhere on the board
/ALL_AMPS/VD.P4: U4.37 (VOUT4+); also elsewhere on the board
/ALL_AMPS/VD.P5: U4.35 (VOUT5+); also elsewhere on the board
/ALL_AMPS/VD.P6: U4.33 (VOUT6+); also elsewhere on the board
/ALL_AMPS/VD.P7: U4.31 (VOUT7+); also elsewhere on the board
/ALL_AMPS/VD.P8: U4.29 (VOUT8+); also elsewhere on the board
/DAC0/SAI_FS: R134.1, R135.1; also elsewhere on the board
/DAC0/SAI_SCK: R138.1, R139.1; also elsewhere on the board
/DAC0/SAI_SD: R142.1; also elsewhere on the board
/DAC1/SAI_SD: R143.1; also elsewhere on the board
/DAC2/SAI_FS: R136.1; also elsewhere on the board
/DAC2/SAI_SCK: R140.1; also elsewhere on the board
/DAC3/SAI_SD: R144.1; also elsewhere on the board
AMUTEI: U2.18 (AMUTEI), U3.18 (AMUTEI), U4.18 (AMUTEI); also elsewhere on the board
AMUTEO: R108.1, R109.1, R110.1; also elsewhere on the board
GND: C7.2, C8.2, C9.2, C10.2, C11.2, C12.2, C13.2, C14.2, C15.2, C16.2, C17.2, C18.2, C19.2, C20.2, C21.2, C22.2, C23.2, C24.2, R2.2, R3.2, R4.2, U2.1 (RSV2_1), U2.3 (RSV2_2), U2.5 (RSV2_3), U2.9 (DIN2), U2.10 (DIN3), U2.11 (DIN4), U2.13 (DGND), U2.22 (MS/ADR0/RSV), U2.23 (TEST/ADR1/RSV), U2.27 (AGND1), U2.28 (RSV2_4), U2.45 (RSV2_5), U2.46 (AGND2), U2.48 (RSV2_6), U2.49 (EP), U3.1 (RSV2_1), U3.3 (RSV2_2), U3.5 (RSV2_3), U3.9 (DIN2), U3.10 (DIN3), U3.11 (DIN4), U3.13 (DGND), U3.22 (MS/ADR0/RSV), U3.27 (AGND1), U3.28 (RSV2_4), U3.45 (RSV2_5), U3.46 (AGND2), U3.48 (RSV2_6), U3.49 (EP), U4.1 (RSV2_1), U4.3 (RSV2_2), U4.5 (RSV2_3), U4.9 (DIN2), U4.10 (DIN3), U4.11 (DIN4), U4.13 (DGND), U4.27 (AGND1), U4.28 (RSV2_4), U4.45 (RSV2_5), U4.46 (AGND2), U4.48 (RSV2_6), U4.49 (EP); also elsewhere on the board
I2C1_SCL: U2.21 (MC/SCL/FMT), U3.21 (MC/SCL/FMT), U4.21 (MC/SCL/FMT); also elsewhere on the board
I2C1_SDA: U2.20 (MD/SDA/DEMP), U3.20 (MD/SDA/DEMP), U4.20 (MD/SDA/DEMP); also elsewhere on the board
unnamed: R108.2, U2.19 (AMUTEO)
unnamed: R138.2, U2.7 (BCK)
unnamed: R142.2, U2.8 (DIN1)
unnamed: R134.2, U2.6 (LRCK)
unnamed: R2.1, U2.24 (MODE)
unnamed: R146.2, U2.14 (SCKI)
unnamed: C11.1, U2.26 (VCOM)
unnamed: R109.2, U3.19 (AMUTEO)
unnamed: R139.2, U3.7 (BCK)
unnamed: R143.2, U3.8 (DIN1)
unnamed: R135.2, U3.6 (LRCK)
unnamed: R3.1, U3.24 (MODE)
unnamed: R147.2, U3.14 (SCKI)
unnamed: C17.1, U3.26 (VCOM)
unnamed: R110.2, U4.19 (AMUTEO)
unnamed: R140.2, U4.7 (BCK)
unnamed: R144.2, U4.8 (DIN1)
unnamed: R136.2, U4.6 (LRCK)
unnamed: R4.1, U4.24 (MODE)
unnamed: R148.2, U4.14 (SCKI)
unnamed: C23.1, U4.26 (VCOM)
SAI1_MCLK: R146.1, R147.1, R148.1; also elsewhere on the board
~RST: U2.15 (~RST), U3.15 (~RST), U4.15 (~RST); also elsewhere on the board

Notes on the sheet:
Analog
